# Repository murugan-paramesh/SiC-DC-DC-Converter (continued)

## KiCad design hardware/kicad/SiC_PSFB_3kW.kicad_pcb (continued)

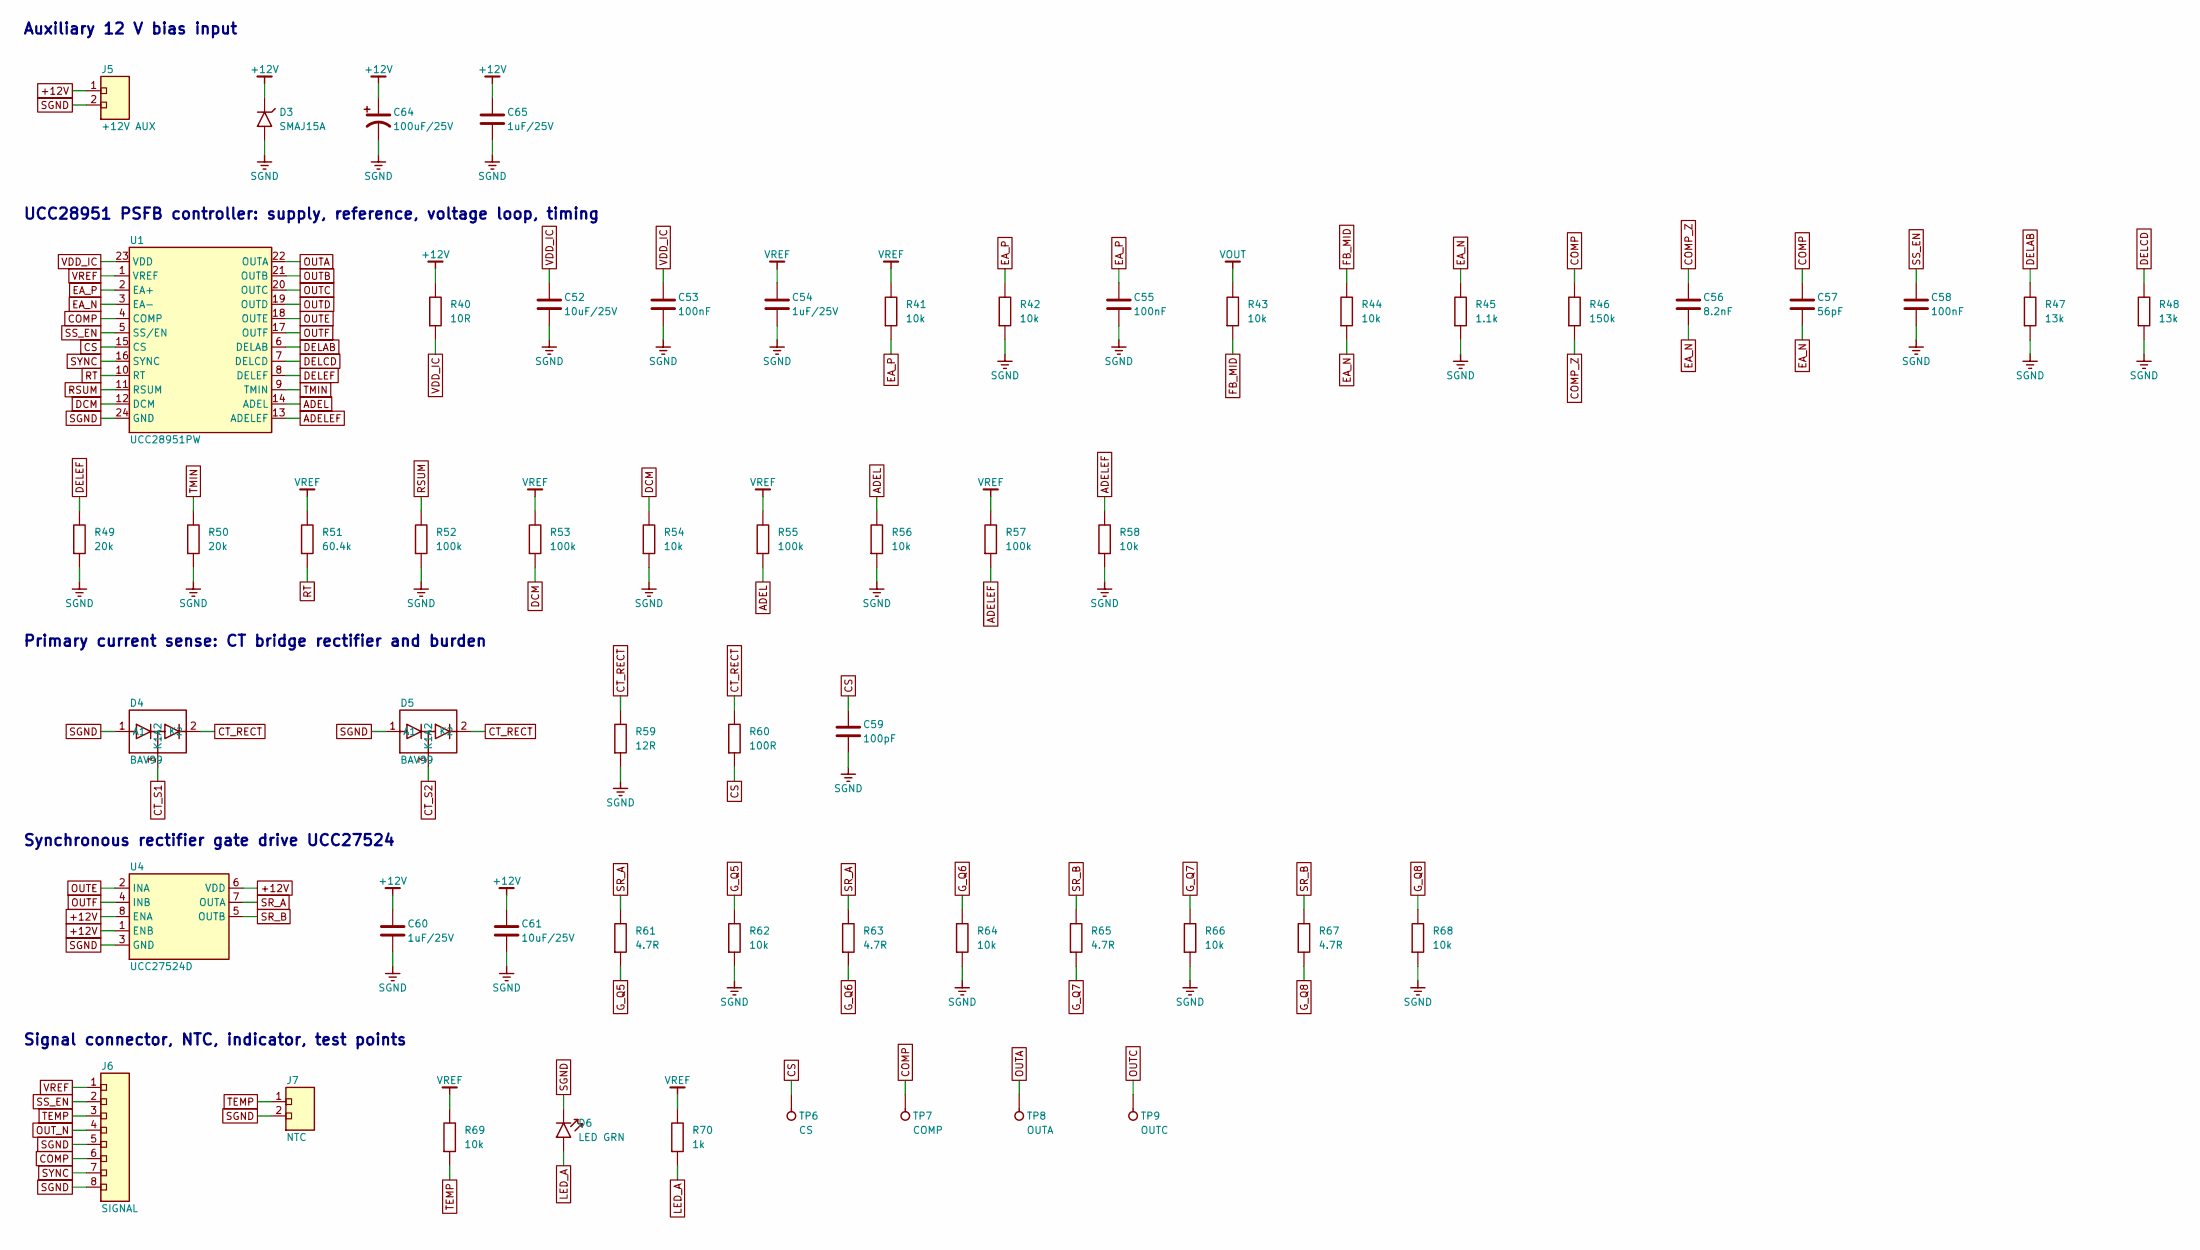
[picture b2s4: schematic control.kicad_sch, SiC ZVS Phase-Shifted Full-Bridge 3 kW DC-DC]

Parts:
C52, C61: 10uF/25V; C_1206
C53, C55, C58: 100nF; C_0603
C54, C60, C65: 1uF/25V; C_0603
C56: 8.2nF; C_0603
C57: 56pF; C_0603
C59: 100pF; C_0603
C64: 100uF/25V; C_Radial_D8_P3.5
D3: SMAJ15A; D_SMA; MPN Littelfuse SMAJ15A
D4, D5: BAV99; SOT-23
D6: LED GRN; LED_0805
J5: +12V AUX; TerminalBlock_1x02_P5.08
J6: SIGNAL; PinHeader_1x08_P2.54
J7: NTC; PinHeader_1x02_P2.54
R40: 10R; R_0805
R41, R42, R54, R56, R58, R62, R64, R66, R68, R69: 10k; R_0603
R43, R44: 10k; R_0805
R45: 1.1k; R_0603
R46: 150k; R_0603
R47, R48: 13k; R_0603
R49, R50: 20k; R_0603
R51: 60.4k; R_0603
R52, R53, R55, R57: 100k; R_0603
R59: 12R; R_0805
R60: 100R; R_0603
R61, R63, R65, R67: 4.7R; R_0805
R70: 1k; R_0603
TP6: CS; TestPoint
TP7: COMP; TestPoint
TP8: OUTA; TestPoint
TP9: OUTC; TestPoint
U1: UCC28951PW; TSSOP-24; MPN TI UCC28951PW
U4: UCC27524D; SOIC-8; MPN TI UCC27524D

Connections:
+12V: C60.1, C61.1, C64.1 (+), C65.1, D3.1 (K), J5.1, R40.1, U4.1 (ENB), U4.6 (VDD), U4.8 (ENA); also elsewhere on the board
ADEL: R55.2, R56.1, U1.14 (ADEL)
ADELEF: R57.2, R58.1, U1.13 (ADELEF)
COMP: C57.1, J6.6, R46.1, TP7.1, U1.4 (COMP)
COMP_Z: C56.1, R46.2
CS: C59.1, R60.2, TP6.1, U1.15 (CS)
CT_RECT: D4.2 (K2), D5.2 (K2), R59.1, R60.1
CT_S1: D4.3 (K1A2); also elsewhere on the board
CT_S2: D5.3 (K1A2); also elsewhere on the board
DCM: R53.2, R54.1, U1.12 (DCM)
DELAB: R47.1, U1.6 (DELAB)
DELCD: R48.1, U1.7 (DELCD)
DELEF: R49.1, U1.8 (DELEF)
EA_N: C56.2, C57.2, R44.2, R45.1, U1.3 (EA-)
EA_P: C55.1, R41.2, R42.1, U1.2 (EA+)
FB_MID: R43.2, R44.1
G_Q5: R61.2, R62.1; also elsewhere on the board
G_Q6: R63.2, R64.1; also elsewhere on the board
G_Q7: R65.2, R66.1; also elsewhere on the board
G_Q8: R67.2, R68.1; also elsewhere on the board
LED_A: D6.2 (A), R70.2
OUTA: TP8.1, U1.22 (OUTA); also elsewhere on the board
OUTB: U1.21 (OUTB); also elsewhere on the board
OUTC: TP9.1, U1.20 (OUTC); also elsewhere on the board
OUTD: U1.19 (OUTD); also elsewhere on the board
OUTE: U1.18 (OUTE), U4.2 (INA)
OUTF: U1.17 (OUTF), U4.4 (INB)
OUT_N: J6.4; also elsewhere on the board
RSUM: R52.1, U1.11 (RSUM)
RT: R51.2, U1.10 (RT)
SGND: C52.2, C53.2, C54.2, C55.2, C58.2, C59.2, C60.2, C61.2, C64.2 (-), C65.2, D3.2 (A), D4.1 (A1), D5.1 (A1), D6.1 (K), J5.2, J6.5, J6.8, J7.2, R42.2, R45.2, R47.2, R48.2, R49.2, R50.2, R52.2, R54.2, R56.2, R58.2, R59.2, R62.2, R64.2, R66.2, R68.2, U1.24 (GND), U4.3 (GND); also elsewhere on the board
SR_A: R61.1, R63.1, U4.7 (OUTA)
SR_B: R65.1, R67.1, U4.5 (OUTB)
SS_EN: C58.1, J6.2, U1.5 (SS/EN)
SYNC: J6.7, U1.16 (SYNC)
TEMP: J6.3, J7.1, R69.2
TMIN: R50.1, U1.9 (TMIN)
VDD_IC: C52.1, C53.1, R40.2, U1.23 (VDD)
VOUT: R43.1; also elsewhere on the board
VREF: C54.1, J6.1, R41.1, R51.1, R53.1, R55.1, R57.1, R69.1, R70.1, U1.1 (VREF)

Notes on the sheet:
Auxiliary 12 V bias input
UCC28951 PSFB controller: supply, reference, voltage loop, timing
Primary current sense: CT bridge rectifier and burden
Synchronous rectifier gate drive UCC27524
Signal connector, NTC, indicator, test points

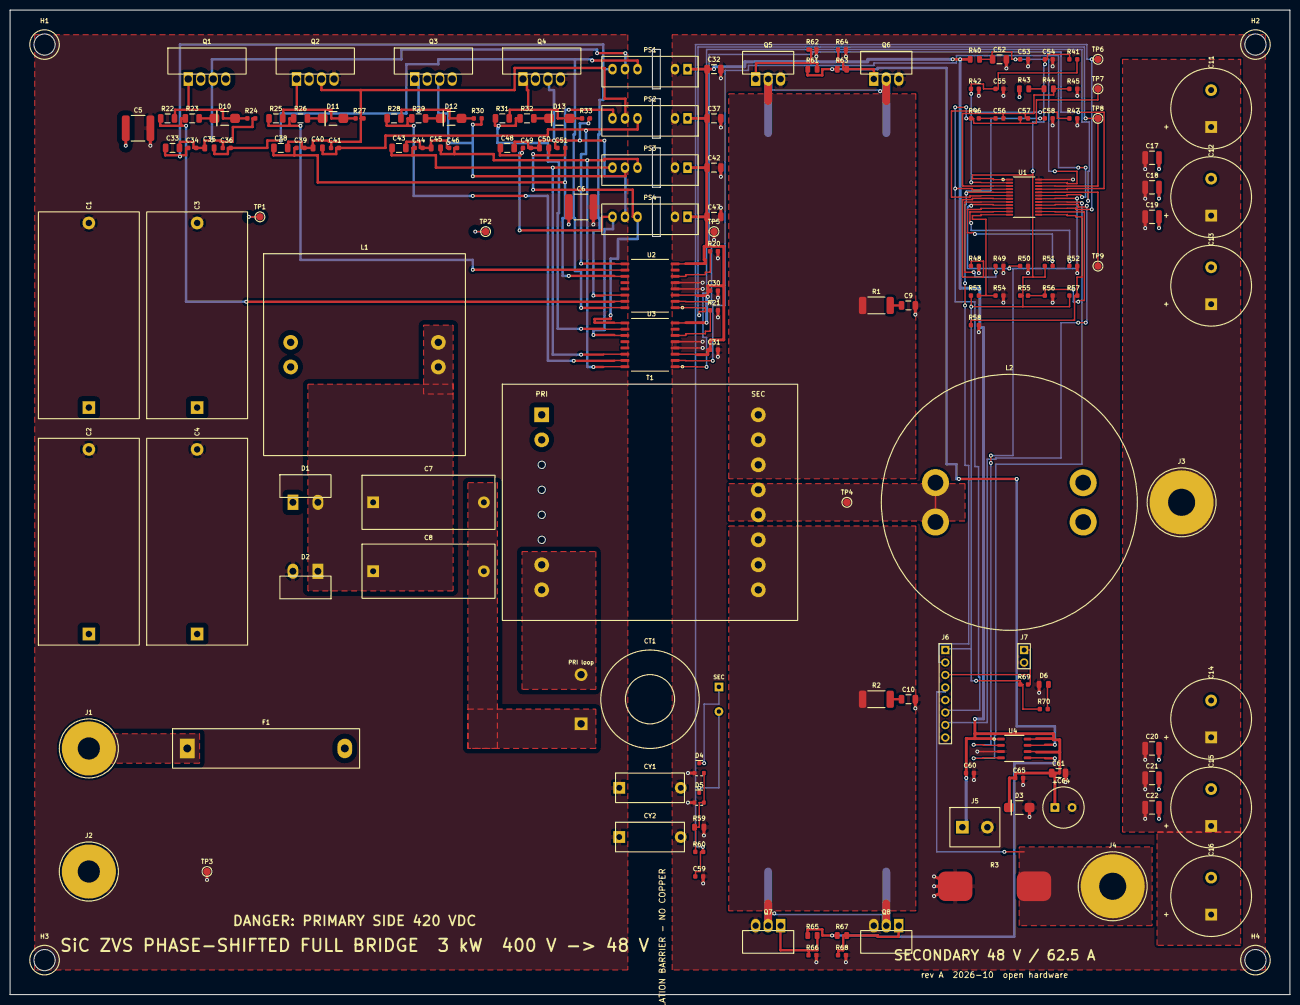
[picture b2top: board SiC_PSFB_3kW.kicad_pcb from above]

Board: 4 copper layers, 260.0 x 200.0 mm, 157 parts (0 on the bottom side), 79 nets.

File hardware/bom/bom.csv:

qty,refs,value,footprint,mpn,description
4,"C1, C2, C3, C4",10uF/450V,C_Film_P37.5,TDK B32778G4106K,DC-link film capacitor
6,"C11, C12, C13, C14, C15, C16",470uF/63V,C_Radial_D16_P7.5,Nichicon UHW1J471MHD,"Output electrolytic, low ESR"
6,"C17, C18, C19, C20, C21, C22",10uF/100V,C_1210,TDK CGA6P3X7S2A106K,Output MLCC X7S
5,"C30, C31, C54, C60, C65",1uF/25V,C_0603,,U2 VCCI decoupling
10,"C32, C33, C37, C38, C42, C43, C47, C48, C52, C61",10uF/25V,C_1206,,PS1 input capacitor
8,"C34, C36, C39, C41, C44, C46, C49, C51",1uF/50V,C_0603,,Q1 +15 V bias HF
4,"C35, C40, C45, C50",4.7uF/25V,C_0805,,Q1 -3 V bias bulk
2,"C5, C6",470nF/630V,C_2220,TDK CGA9P4X7T2J474K,Bridge HF decoupling MLCC
3,"C53, C55, C58",100nF,C_0603,,VDD HF
1,C56,8.2nF,C_0603,,Type-II compensation Cz
1,C57,56pF,C_0603,,Type-II compensation Cp
1,C59,100pF,C_0603,,"CS filter, C0G"
1,C64,100uF/25V,C_Radial_D8_P3.5,,Bias bulk capacitor
2,"C7, C8",4.7uF/250V,C_Film_P22.5,TDK B32674D3475K,DC blocking capacitor
2,"C9, C10",470pF/250V,C_1206,,"SR snubber capacitor, C0G"
1,CT1,CT 1:100,CT_Toroid_Straddle,Magnetics ZW42908TC + 100T AWG32 (or Pulse PA3855.100NL class),"Primary current transformer, 1-turn insulated primary lead"
2,"CY1, CY2",2.2nF Y1,C_Y1_P12.5,Vishay VY1222M63Y5UQ63V0,Y1 safety capacitor across the barrier
2,"D1, D2",C3D04065A,TO-220-2_Vertical,Wolfspeed C3D04065A,Primary clamp diode to VBUS (SiC Schottky 650 V)
4,"D10, D11, D12, D13",SS14,D_SMA,Vishay SS14,Q1 turn-off steering diode
1,D3,SMAJ15A,D_SMA,Littelfuse SMAJ15A,Bias input TVS
2,"D4, D5",BAV99,SOT-23,,CT rectifier bridge half
1,D6,LED GRN,LED_0805,,VREF OK indicator
1,F1,15A/500V,Fuse_6.3x32_Clips,Littelfuse 0215015.MXP,"Input fuse 6.3x32 ceramic, 15 A 500 V"
1,J1,VIN+,Lug_M4,,Input terminal + (M4 ring lug)
1,J2,VIN-,Lug_M4,,Input terminal - (M4 ring lug)
1,J3,VOUT+,Lug_M5,,Output terminal + (M5 ring lug)
1,J4,VOUT-,Lug_M5,,Output terminal - (M5 ring lug)
1,J5,+12V AUX,TerminalBlock_1x02_P5.08,,Auxiliary 12 V bias input (secondary referenced)
1,J6,SIGNAL,PinHeader_1x08_P2.54,,"Signal header: 1 VREF, 2 EN, 3 TEMP, 4 IMON- (shunt), 5 IMON+ (SGND), 6 COMP, 7 SYNC, 8 GND"
1,J7,NTC,PinHeader_1x02_P2.54,,Heatsink NTC 10k
1,L1,12uH Lr,Inductor_ETD39_Lr,custom ETD39/3C95 10T litz,Resonant (shim) inductor
1,L2,6.8uH/70A,Inductor_Toroid_D52_Lo,"custom 2x Magnetics 77439-A7, 5T flat wire",Output inductor
4,"PS1, PS2, PS3, PS4",R12P21503D,SIP-7_IsoDCDC,RECOM R12P21503D,Isolated +15/-3 V gate bias for Q1
4,"Q1, Q2, Q3, Q4",C3M0060065K,TO-247-4_Vertical,Wolfspeed C3M0060065K,"SiC MOSFET 650 V 60 mOhm, leg A high side"
4,"Q5, Q6, Q7, Q8",IPP110N20N3 G,TO-220-3_Vertical,Infineon IPP110N20N3 G,"Synchronous rectifier A1, 200 V 10.7 mOhm"
2,"R1, R2",10R/2W,R_2512,,SR snubber resistor
2,"R20, R21",2.2k,R_0603,,Driver dead-time (22 ns safety)
4,"R22, R25, R28, R31",5.1R,R_1206,,Q1 turn-on gate resistor
4,"R23, R26, R29, R32",2.2R,R_1206,,Q1 turn-off gate resistor
14,"R24, R27, R30, R33, R41, R42, R54, R56, R58, R62, R64, R66, R68, R69",10k,R_0603,,Q1 gate-source bleed
1,R3,0.5mR,R_Shunt_8518,Vishay WSBS8518L5000JK,Output current shunt 0.5 mOhm
1,R40,10R,R_0805,,VDD filter
2,"R43, R44",10k,R_0805,,Output voltage divider upper 1
1,R45,1.1k,R_0603,,Output voltage divider lower
1,R46,150k,R_0603,,Type-II compensation Rz
2,"R47, R48",13k,R_0603,,A/B leg delay
2,"R49, R50",20k,R_0603,,SR (E/F) delay
1,R51,60.4k,R_0603,,Oscillator: 100 kHz (verify against datasheet equation)
4,"R52, R53, R55, R57",100k,R_0603,,Slope compensation
1,R59,12R,R_0805,,CT burden resistor
1,R60,100R,R_0603,,CS filter
4,"R61, R63, R65, R67",4.7R,R_0805,,Q5 gate resistor
1,R70,1k,R_0603,,LED resistor
1,T1,ETD59 18:3:3,Transformer_ETD59_PSFB,"custom, see docs/06","Main transformer ETD59/3C95, 18:3:3, reinforced insulation"
1,U1,UCC28951PW,TSSOP-24,TI UCC28951PW,PSFB controller
2,"U2, U3",UCC21520DW,SOIC-16W,TI UCC21520DW,"Isolated dual gate driver, Q1/Q2"
1,U4,UCC27524D,SOIC-8,TI UCC27524D,Dual 5 A SR gate driver
